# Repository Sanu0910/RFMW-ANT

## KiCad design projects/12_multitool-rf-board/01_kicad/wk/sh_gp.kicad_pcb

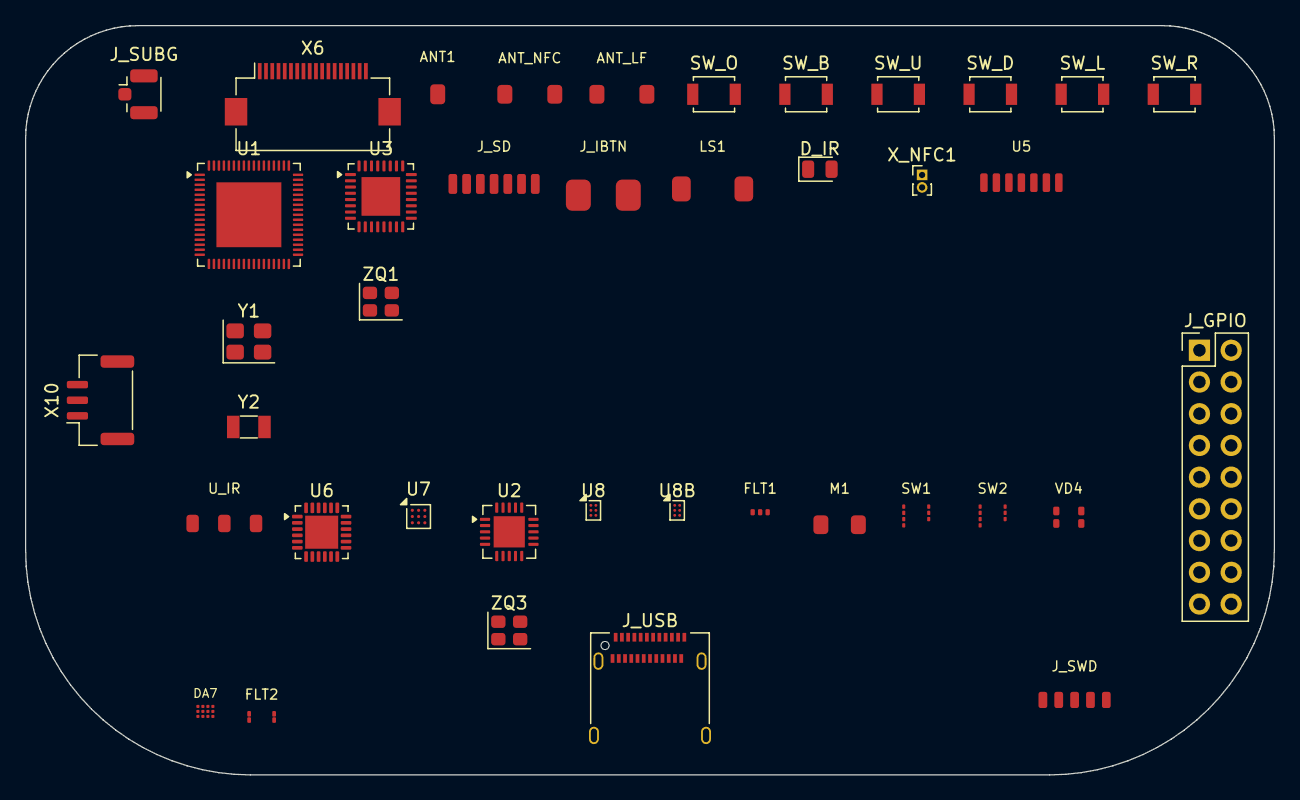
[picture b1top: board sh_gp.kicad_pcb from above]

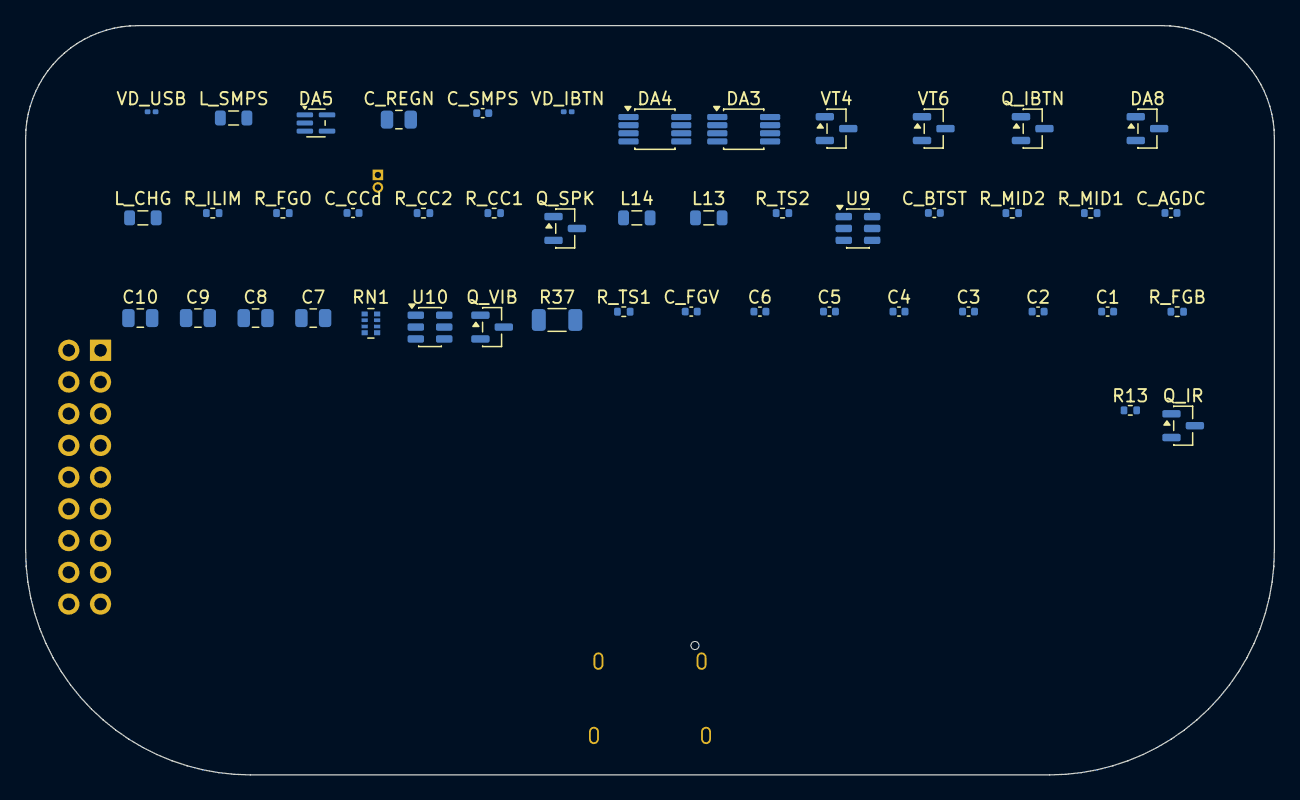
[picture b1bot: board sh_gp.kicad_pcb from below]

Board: 4 copper layers, 100.0 x 60.0 mm, 86 parts (46 on the bottom side), 104 nets, no tracks yet.

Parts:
ANT1: 2.4GHz; Antenna_Chip
ANT_LF: 125kHz coil; RFID_125k_Coil
ANT_NFC: 13.56MHz loop; NFC_Loop_Antenna
C1, C2, C3, C4, C5, C6: 100nF; C_0402_1005Metric
C7, C8, C9, C10: 10uF; C_0805_2012Metric
C_AGDC: 1uF; C_0402_1005Metric
C_BTST: 47nF; C_0402_1005Metric
C_CCd: 100nF; C_0402_1005Metric
C_FGV: 2.2uF; C_0402_1005Metric
C_REGN: 4.7uF; C_0805_2012Metric
C_SMPS: 2.2uF; C_0402_1005Metric
DA3, DA4: LMV358; VSSOP-8_3x3mm_P0.65mm
DA5: LMV331; SOT-353_SC-70-5
DA7: LP5562; LP5562_DSBGA12
DA8: RS3221-3.3; SOT-23
D_IR: IR LED x3; LED_0805_2012Metric
FLT1: BLE filter; RF_filter
FLT2: balun; Johanson_0310_Balun
J_GPIO: header 2x9; PinHeader_2x09_P2.54mm_Vertical
J_IBTN: iButton; iButton_Contacts
J_SD: microSD; microSD_7p
J_SUBG: ANT; U.FL_Hirose_U.FL-R-SMT-1_Vertical
J_SWD: SWD; TagConnect_TC2030
J_USB: USB-C; USB_C_Receptacle_Amphenol_12401610E4-2A
L13, L14: 470nH; L_0805_2012Metric
LS1: speaker; Speaker_2p
L_CHG: 2.2uH; L_0805_2012Metric
L_SMPS: 10uH; L_0805_2012Metric
M1: vibro; Vibro_2p
Q_IBTN: 1W driver; SOT-23
Q_IR: drive; SOT-23
Q_SPK: drive; SOT-23
Q_VIB: drive; SOT-23
R13: 56k; R_0402_1005Metric
R37: 10m; R_1206_3216Metric
RN1: 51x4; R_Array_Convex_4x0402
R_CC1, R_CC2: 5.1k; R_0402_1005Metric
R_FGB: 10k; R_0402_1005Metric
R_FGO: 10k; R_0402_1005Metric
R_ILIM: 1.1k; R_0402_1005Metric
R_MID1, R_MID2: 33k; R_0402_1005Metric
R_TS1: 5.23k; R_0402_1005Metric
R_TS2: 30.31k; R_0402_1005Metric
SW1, SW2: RFswitch; RF_Switch_TSNP9
SW_B: tact; SW_SPST_B3U-1000P
SW_D: tact; SW_SPST_B3U-1000P
SW_L: tact; SW_SPST_B3U-1000P
SW_O: tact; SW_SPST_B3U-1000P
SW_R: tact; SW_SPST_B3U-1000P
SW_U: tact; SW_SPST_B3U-1000P
U1: STM32WB55RG; QFN-68-1EP_8x8mm_P0.4mm_EP5.2x5.2mm
U2: CC1101; QFN-20-1EP_4x4mm_P0.5mm_EP2.5x2.5mm
U3: ST25R3916; QFN-32-1EP_5x5mm_P0.5mm_EP3.1x3.1mm
U5: ST7565R; Display_ST7565_FFC
U6: BQ25896; QFN-24-1EP_4x4mm_P0.5mm_EP2.65x2.65mm
U7: BQ27220; BGA-9_1.6x1.6mm_Layout3x3_P0.5mm
U8, U8B: LM3281; Texas_DSBGA-6_0.76x1.16mm_Layout2x3_P0.4mm
U9: loadsw; SOT-23-6
U10: ESD; SOT-23-6
U_IR: IR RX; TSOP_IR_3p
VD4: RGB LED; LED_RGB_4p
VD_IBTN: ESD; R_0201_0603Metric
VD_USB: ESD; R_0201_0603Metric
VT4: coildrv P; SOT-23
VT6: coildrv N; SOT-23
X6: FFC 18p; Hirose_FH12-18S-0.5SH_1x18-1MP_P0.50mm_Horizontal
X10: BAT+NTC; JST_GH_SM03B-GHS-TB_1x03-1MP_P1.25mm_Horizontal
X_NFC1: ANT conn; PinHeader_1x02_P1.00mm_Vertical
Y1: 32MHz; Crystal_SMD_3225-4Pin_3.2x2.5mm
Y2: 32.768kHz; Crystal_SMD_3215-2Pin_3.2x1.5mm
ZQ1: 27.12MHz; Crystal_SMD_2520-4Pin_2.5x2.0mm
ZQ3: 26MHz; Crystal_SMD_2520-4Pin_2.5x2.0mm

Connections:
+3V3: C1.1, C2.1, C3.1, C7.1, DA7.A2, DA7.C3, J_GPIO.1, J_SD.VDD, J_SWD.VCC, L13.2, SW1.VDD, SW2.VDD, U1.1, U1.13, U1.14, U1.30, U1.33, U1.44, U1.45, U1.55, U1.68, U2.4, U2.9, U2.11, U2.14, U2.15, U2.18, U3.1, U3.3, U3.7, U3.8, U3.9, U3.10, U3.11, U3.14, U5.VDD, U8.A1, U8.C1, U9.1, U_IR.VS, VD4.A
+3V3_EXT: L14.2, U8B.A1, X6.3
+3V3_PERIPH: C4.1, C10.1, U9.6
A3V3: DA3.8, DA4.8, DA5.5, R_MID1.1
BLE_ANT: ANT1.1, FLT1.OUT
BTN_BACK: SW_B.1, U1.2
BTN_DOWN: SW_D.1, U1.50
BTN_LEFT: SW_L.1, U1.29
BTN_OK: SW_O.1, U1.5
BTN_RIGHT: SW_R.1, U1.46
BTN_UP: SW_U.1, U1.28
CC1101_CS: U1.61, U2.7
CC1101_GDO0: U1.16, U2.6
CC_DCOUPL: C_CCd.1, U2.5
CC_RBIAS: R13.1, U2.17
CC_XO1: U2.8, ZQ3.1
CC_XO2: U2.10, ZQ3.2
CHG_BTST: C_BTST.2, U6.21
CHG_ILIM: R_ILIM.1, U6.10
CHG_REGN: C_REGN.1, R_TS1.1, U6.22
CHG_SW: C_BTST.1, L_CHG.1, U6.19, U6.20
CHG_TS: R_TS1.2, R_TS2.1, U6.11
DISP_CS: U1.59, U5.CS
DISP_DI: U1.39, U5.A0
DISP_RST: U1.38, U5.RST
EXT_PA4: J_GPIO.4, U1.19
EXT_PA6: J_GPIO.3, U1.21
EXT_PA7: J_GPIO.2, U1.22
EXT_PB2: J_GPIO.6, U1.27
EXT_PB3: J_GPIO.5, U1.63
EXT_PC0: J_GPIO.9, U1.9
EXT_PC1: J_GPIO.8, U1.10
EXT_PC3: J_GPIO.7, U1.12
FG_BIN: R_FGB.1, U7.B1
FG_GPOUT: R_FGO.1, U7.A1
FG_VDD: C_FGV.1, R_FGO.2, U7.B3
GND: C1.2, C2.2, C3.2, C4.2, C5.2, C6.2, C7.2, C8.2, C9.2, C10.2, C_AGDC.2, C_CCd.2, C_FGV.2, C_REGN.2, C_SMPS.2, DA3.4, DA4.4, DA5.2, DA7.B1, DA7.B2, DA7.B3, DA8.1, D_IR.1, FLT1.GND, FLT2.GND, J_GPIO.18, J_IBTN.GND, J_SD.VSS, J_SUBG.2, J_SWD.GND, J_USB.A1, J_USB.S1, LS1.-, M1.-, Q_IBTN.2, Q_IR.2, Q_SPK.2, Q_VIB.2, R13.2, R_CC1.2, R_CC2.2, R_FGB.2, R_ILIM.2, R_MID2.2, R_TS2.2, SW1.GND, SW2.GND, SW_B.2, SW_D.2, SW_L.2, SW_O.2, SW_R.2, SW_U.2, U1.32, U1.42, U1.69, U2.16, U2.19, U2.21, U3.6, U3.12, U3.16, U3.20, U3.21, U3.26, U3.33, U5.VSS, U6.9, U6.17, U6.18, U6.25, U7.B2, U7.C2, U8.C2, U8B.C2, U9.2, U10.2, U_IR.GND, VD_IBTN.2, VD_USB.2, VT6.2, X6.6, X6.8, X10.3
HSE_IN: U1.35, Y1.1
HSE_OUT: U1.34, Y1.2
I2C_PWR_SCL: DA7.C2, J_GPIO.15, U1.24, U6.5, U7.A3
I2C_PWR_SDA: DA7.C1, J_GPIO.14, U1.51, U6.6, U7.A2
IBTN: J_IBTN.DATA, Q_IBTN.1, U1.48, VD_IBTN.1, X6.14
IR_LED_A: D_IR.2, Q_IR.3
IR_RX: U1.15, U_IR.OUT, X6.17
IR_TX: Q_IR.1, U1.7, X6.16
LED_B: DA7.A4, VD4.B
LED_G: DA7.B4, VD4.G
LED_R: DA7.C4, VD4.R
LF_A1: DA3.1, DA3.5
LF_A2: DA3.7, DA4.3
LF_A3: DA4.1, DA4.5
LF_COIL_P: ANT_LF.1, VT4.3, VT6.3
LF_ENV: DA4.7, DA5.1
LF_MID: DA3.2, DA5.3, R_MID1.2, R_MID2.1
LF_RX: ANT_LF.2, DA3.3
LSE_IN: U1.3, Y2.1
LSE_OUT: U1.4, Y2.2
NFC_AGDC: C_AGDC.1, U3.24
NFC_ANT_N: ANT_NFC.2, X_NFC1.2
NFC_ANT_P: ANT_NFC.1, X_NFC1.1
NFC_CS: RN1.4, U1.40, U3.29, X6.4
NFC_XTAL1: U3.5, ZQ1.1
NFC_XTAL2: U3.4, ZQ1.2
NRST: J_SWD.NRST, U1.8
PERIPH_EN: U1.18, U8B.C1, U9.3
RFID_CARRIER: U1.17, U3.27, X6.12, X6.18
RFID_CARRIER_OUT: U1.57, VT4.1, X6.11
RFID_RF_IN: DA5.4, U1.26, X6.5
RF_SW_0: SW1.V1, SW2.V1, U1.25
RF_SW_1: SW1.V2, SW2.V2
SD_CD: J_SD.CD, U1.58
SD_CS: J_SD.CS, U1.60
SMPS_FB: C_SMPS.1, L_SMPS.2, U1.41
SMPS_LX: L_SMPS.1, U1.43
SPEAKER: Q_SPK.1, U1.6, X6.15
SPI_D_MISO: J_SD.DO, U1.11
SPI_D_MOSI: J_SD.DI, U1.49, U5.SI
SPI_D_SCK: J_SD.CLK, U1.62, U5.SCL
SPI_R_MISO: RN1.2, U1.64, U2.2, U3.32, X6.9
SPI_R_MOSI: RN1.3, U1.65, U2.20, U3.31, X6.13
SPI_R_SCK: RN1.1, U1.20, U2.1, U3.30, X6.7
SPK_DRV: LS1.+, Q_SPK.3
SUBG_ANT: J_SUBG.1, SW2.RFin
SUBG_F1: SW1.RF1, SW2.RF1
SUBG_F2: SW1.RF2, SW2.RF2
SUBG_RF_N: FLT2.BAL2, U2.13
SUBG_RF_P: FLT2.BAL1, U2.12
SUBG_SE: FLT2.UNBAL, SW1.RFin
SWCLK: J_GPIO.10, J_SWD.SWCLK, U1.56
SWDIO: J_GPIO.11, J_SWD.SWDIO, U1.54
SW_L13: L13.1, U8.B2
SW_L14: L14.1, U8B.B2
UART_RX: J_GPIO.13, U1.67
UART_TX: J_GPIO.12, U1.66
USB_CC1: J_USB.A5, R_CC1.1
USB_CC2: J_USB.B5, R_CC2.1
USB_DM: J_USB.A7, U1.52, U10.1, U10.6, VD_USB.1
USB_DP: J_USB.A6, U1.53, U10.3, U10.4
VBAT: C6.1, C9.1, R37.1, U6.13, U6.14, U7.C3, X10.1
VBAT_SNS: R37.2, U7.C1
VBUS: J_GPIO.16, J_USB.A4, U6.1, U10.5
VIBRO: J_GPIO.17, Q_VIB.1, U1.23, X6.10
VIBRO_DRV: M1.+, Q_VIB.3
VSYS: C5.1, C8.1, DA8.3, L_CHG.2, U6.15, U6.16, U8.A2, U8.B1, U8B.A2, U8B.B1, X6.1, X6.2
